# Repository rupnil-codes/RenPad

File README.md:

# RenPad
RenPad is a compact 8-key productivity macropad powered by the Seeed XIAO RP2040.  
It’s designed as a dedicated Windows control deck with an OLED status display and RGB underglow for everyday workflow speed.

---

## Features
- 8 Cherry MX mechanical keys  
- 128×32 OLED display (status + key feedback)  
- 5× SK6812MINI-E RGB LEDs  
- Seeed XIAO RP2040 microcontroller  
- KMK firmware (CircuitPython-based)  
- Fully custom PCB  
- 3D-printed case  

---

## Project Images

### Schematic

### PCB

### Case Design

**Bottom Case**  

**Top Case**  

### Final Build

---

## System Overview

### MCU
Seeed Studio XIAO RP2040 (Through-hole)

### Inputs
8× Cherry MX mechanical switches

### Outputs
128×32 OLED display (I²C)  
5× SK6812MINI-E RGB LEDs  

---

## Pin Mapping

| Function | GPIO |
|---|---|
| ROW0 | GPIO6 |
| ROW1 | GPIO7 |
| COL0 | GPIO26 |
| COL1 | GPIO27 |
| COL2 | GPIO28 |
| COL3 | GPIO29 |
| RGB Data | GPIO3 |
| OLED SDA | GPIO0 |
| OLED SCL | GPIO1 |

---

## Key Layout (Windows Control Deck)

| Key | Shortcut | Function |
|---|---|---|
| K1 | Win + V | Clipboard history |
| K2 | Alt + Tab | Switch apps |
| K3 | Win + Tab | Task view |
| K4 | Win + E | File Explorer |
| K5 | Ctrl + Shift + Esc | Task Manager |
| K6 | Win + Ctrl + D | New virtual desktop |
| K7 | Win + Ctrl + ← | Desktop left |
| K8 | Win + Ctrl + → | Desktop right |

---

## Bill of Materials (BOM)

| Part | Quantity | Manufacturer | Part Number |
|---|---|---|---|
| Seeed XIAO RP2040 (TH) | 1 | Seeed Studio | 102010428 |
| Cherry MX Mechanical Switch | 8 | Cherry | MX Series |
| 1N4148 Diodes (TH) | 8 | Vishay | 1N4148 |
| SK6812MINI-E LEDs | 5 | WorldSemi | SK6812MINI-E |
| 128×32 OLED Display | 1 | Generic | SSD1306 |
| DSA Keycaps | 8 | Generic | DSA Blank |
| M3 Screws | 4 | Generic | M3 |
| Heatset Inserts | 4 | Generic | M3 |

---

## Firmware
RenPad runs on **KMK (CircuitPython)** firmware.

The firmware supports:
- Key matrix scanning  
- OLED key feedback display  
- RGB underglow effects  
- Windows productivity shortcuts  

Firmware is located in the **Firmware/** folder.

---

## Case
The enclosure is fully 3D-printed and designed in Fusion 360.

It consists of:
- Bottom shell  
- Top plate  
- Heatset insert mounts  

Exported as STEP files in the **CAD/** folder.

---

## Author
Designed and built by **Rupnil.Codes**
Hack Club Hackpad Project
```

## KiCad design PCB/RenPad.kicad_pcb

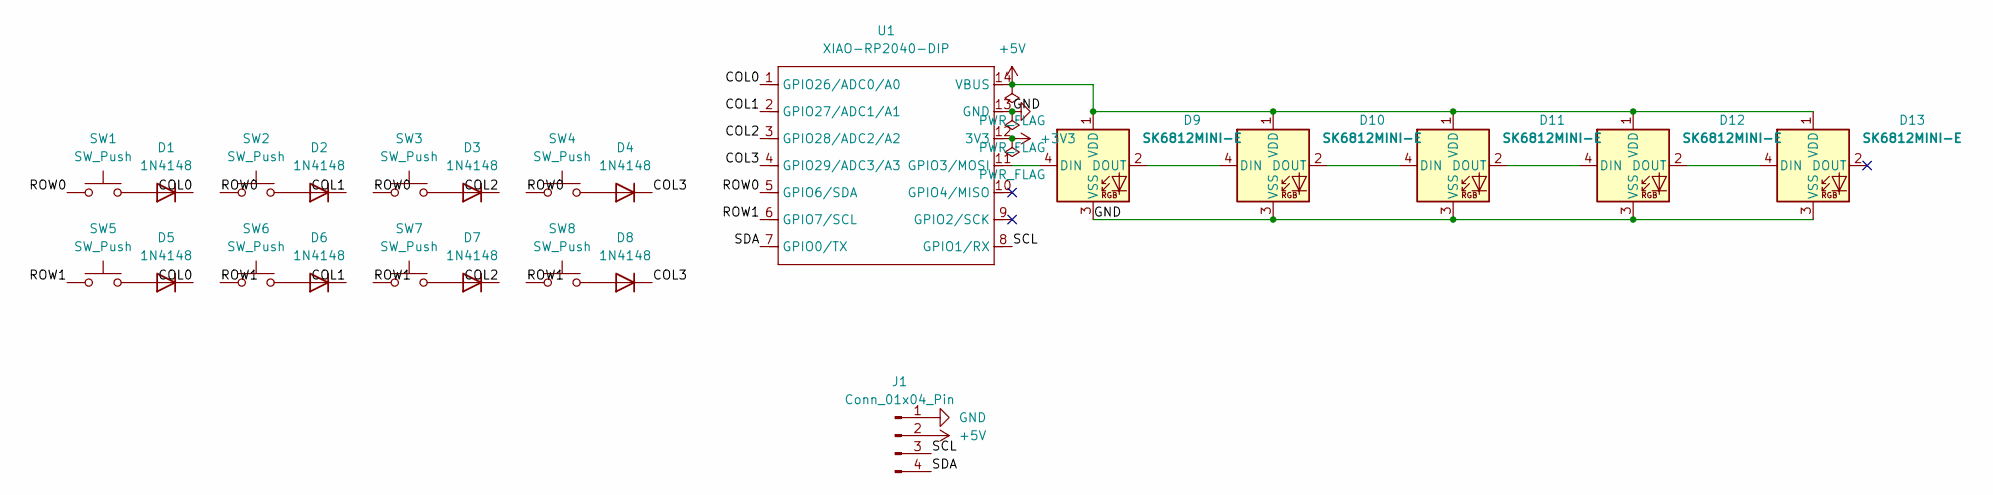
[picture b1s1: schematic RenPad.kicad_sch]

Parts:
D1, D2, D3, D4, D5, D6, D7, D8: 1N4148; D_DO-35_SOD27_P7.62mm_Horizontal
D9, D10, D11, D12, D13: SK6812MINI-E; SK6812MINI-E_fixed
J1: Conn_01x04_Pin; SSD1306-0.91-OLED-4pin-128x32
SW1, SW2, SW3, SW4, SW5, SW6, SW7, SW8: SW_Push; SW_Cherry_MX_1.00u_PCB
U1: XIAO-RP2040-DIP; XIAO-Generic-Hybrid-14P-2.54-21X17.8MM

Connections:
+3V3: U1.12 (3V3)
+5V: D9.1 (VDD), D10.1 (VDD), D11.1 (VDD), D12.1 (VDD), D13.1 (VDD), J1.2, U1.14 (VBUS)
/COL0: D1.1 (K), D5.1 (K), U1.1 (GPIO26/ADC0/A0)
/COL1: D2.1 (K), D6.1 (K), U1.2 (GPIO27/ADC1/A1)
/COL2: D3.1 (K), D7.1 (K), U1.3 (GPIO28/ADC2/A2)
/COL3: D4.1 (K), D8.1 (K), U1.4 (GPIO29/ADC3/A3)
/ROW0: SW1.1, SW2.1, SW3.1, SW4.1, U1.5 (GPIO6/SDA)
/ROW1: SW5.1, SW6.1, SW7.1, SW8.1, U1.6 (GPIO7/SCL)
/SCL: J1.3, U1.8 (GPIO1/RX)
/SDA: J1.4, U1.7 (GPIO0/TX)
GND: D9.3 (VSS), D10.3 (VSS), D11.3 (VSS), D12.3 (VSS), D13.3 (VSS), J1.1, U1.13 (GND)
unnamed: D1.2 (A), SW1.2
unnamed: D2.2 (A), SW2.2
unnamed: D3.2 (A), SW3.2
unnamed: D4.2 (A), SW4.2
unnamed: D5.2 (A), SW5.2
unnamed: D6.2 (A), SW6.2
unnamed: D7.2 (A), SW7.2
unnamed: D8.2 (A), SW8.2
unnamed: D9.4 (DIN), U1.11 (GPIO3/MOSI)
unnamed: D9.2 (DOUT), D10.4 (DIN)
unnamed: D10.2 (DOUT), D11.4 (DIN)
unnamed: D11.2 (DOUT), D12.4 (DIN)
unnamed: D12.2 (DOUT), D13.4 (DIN)

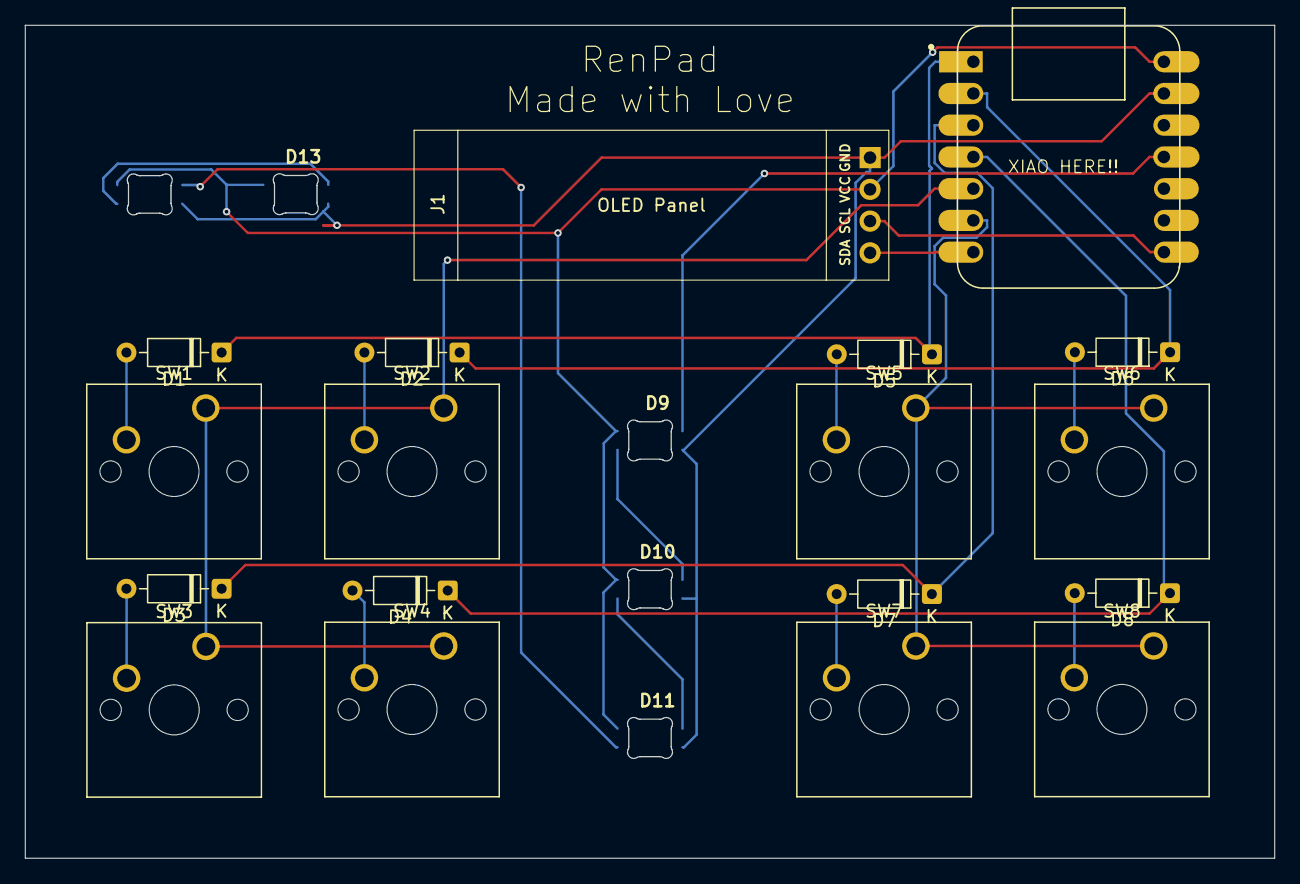
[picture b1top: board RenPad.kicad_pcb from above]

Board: 2 copper layers, 100.0 x 66.6 mm, 23 parts (0 on the bottom side), 23 nets.

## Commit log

2026-02-18 RenPad V1
    Pushed the Full RenPad Hackpad!!
